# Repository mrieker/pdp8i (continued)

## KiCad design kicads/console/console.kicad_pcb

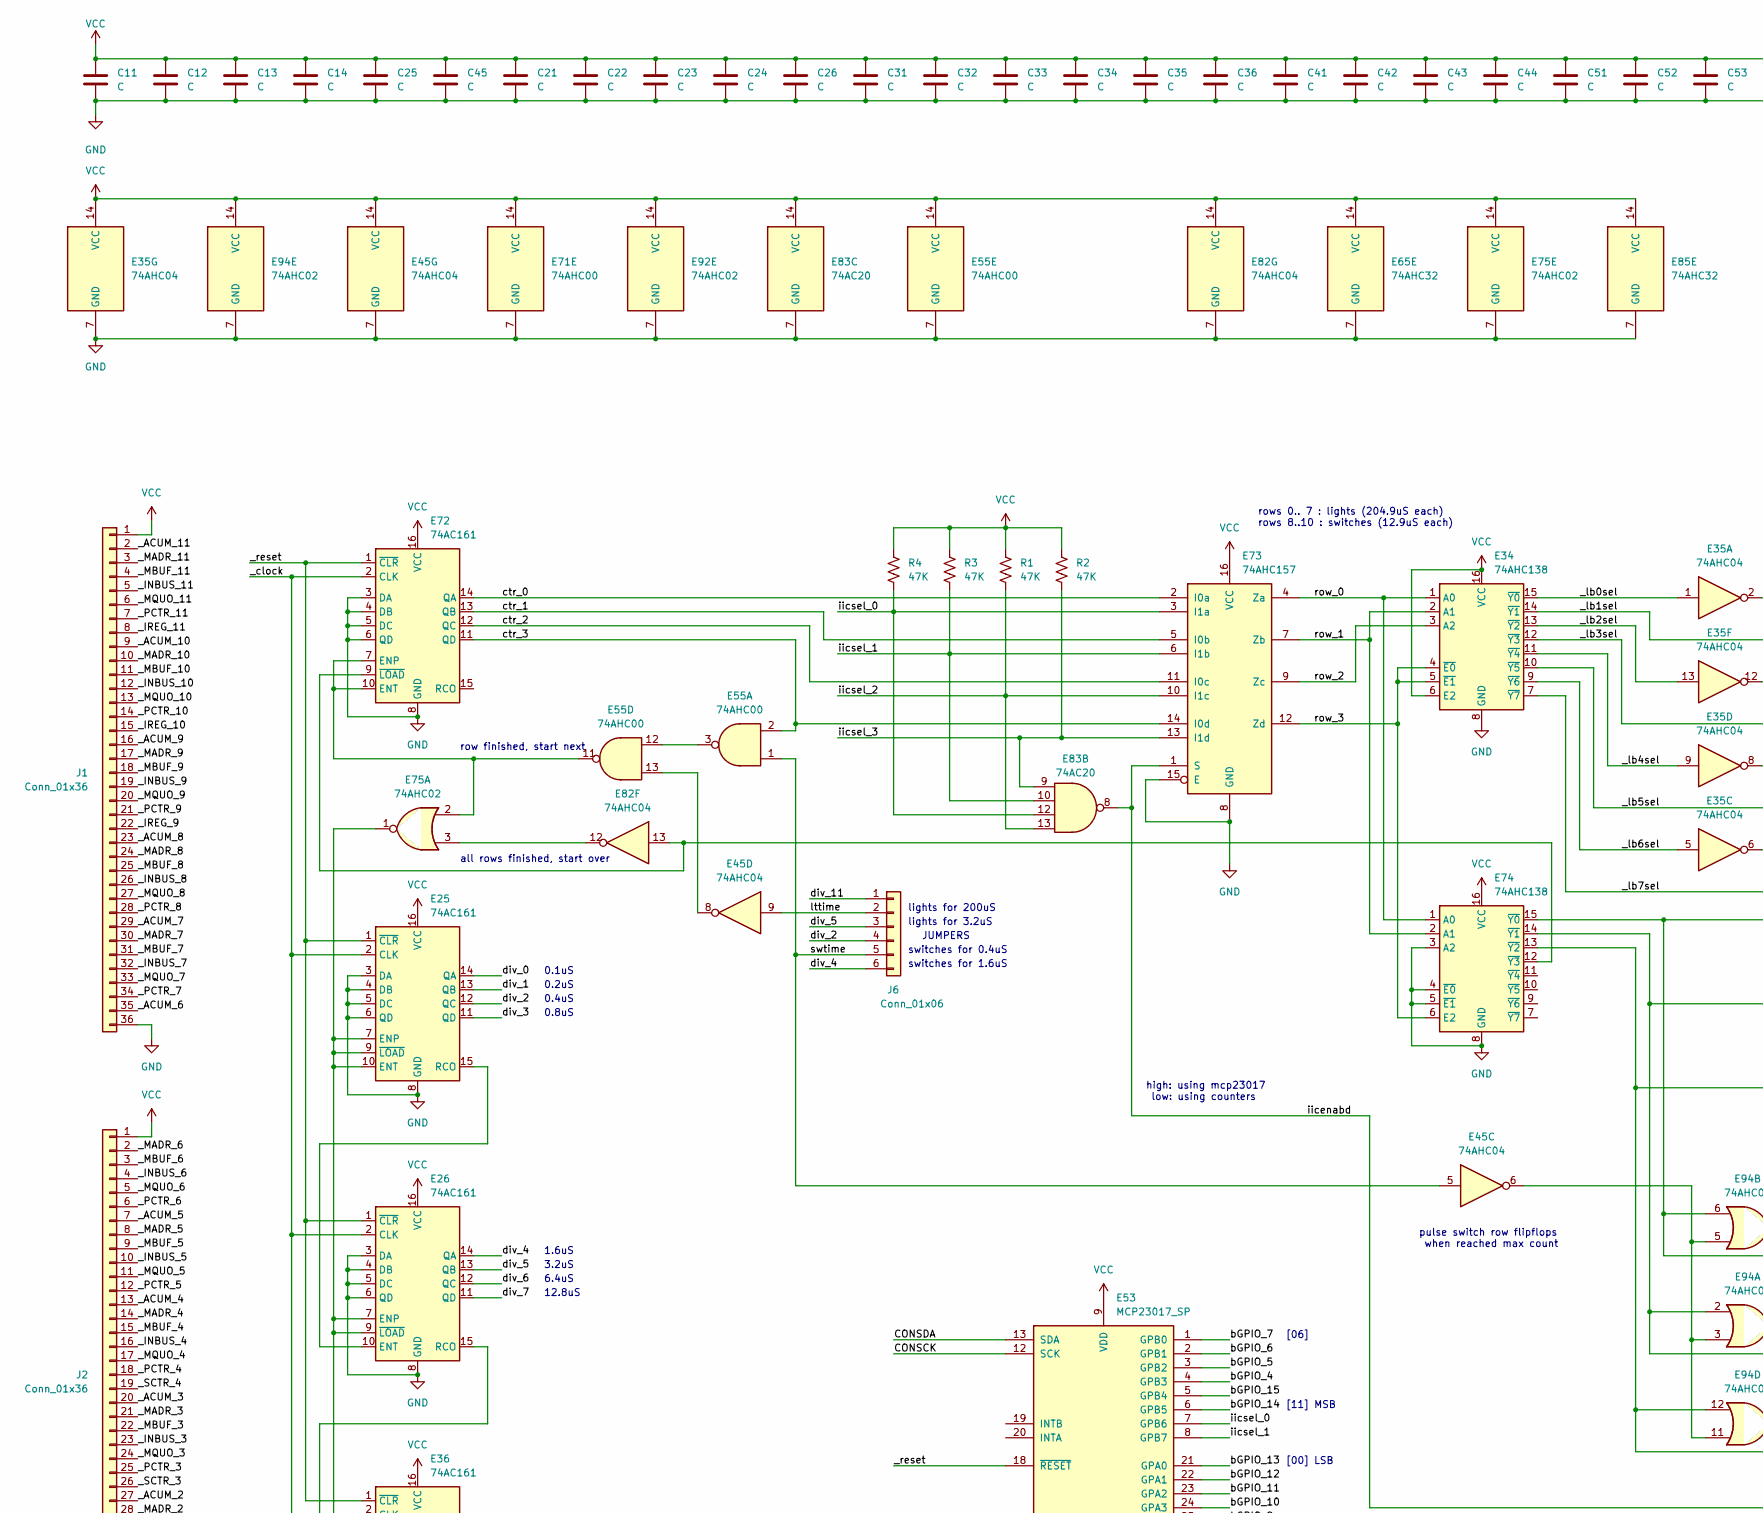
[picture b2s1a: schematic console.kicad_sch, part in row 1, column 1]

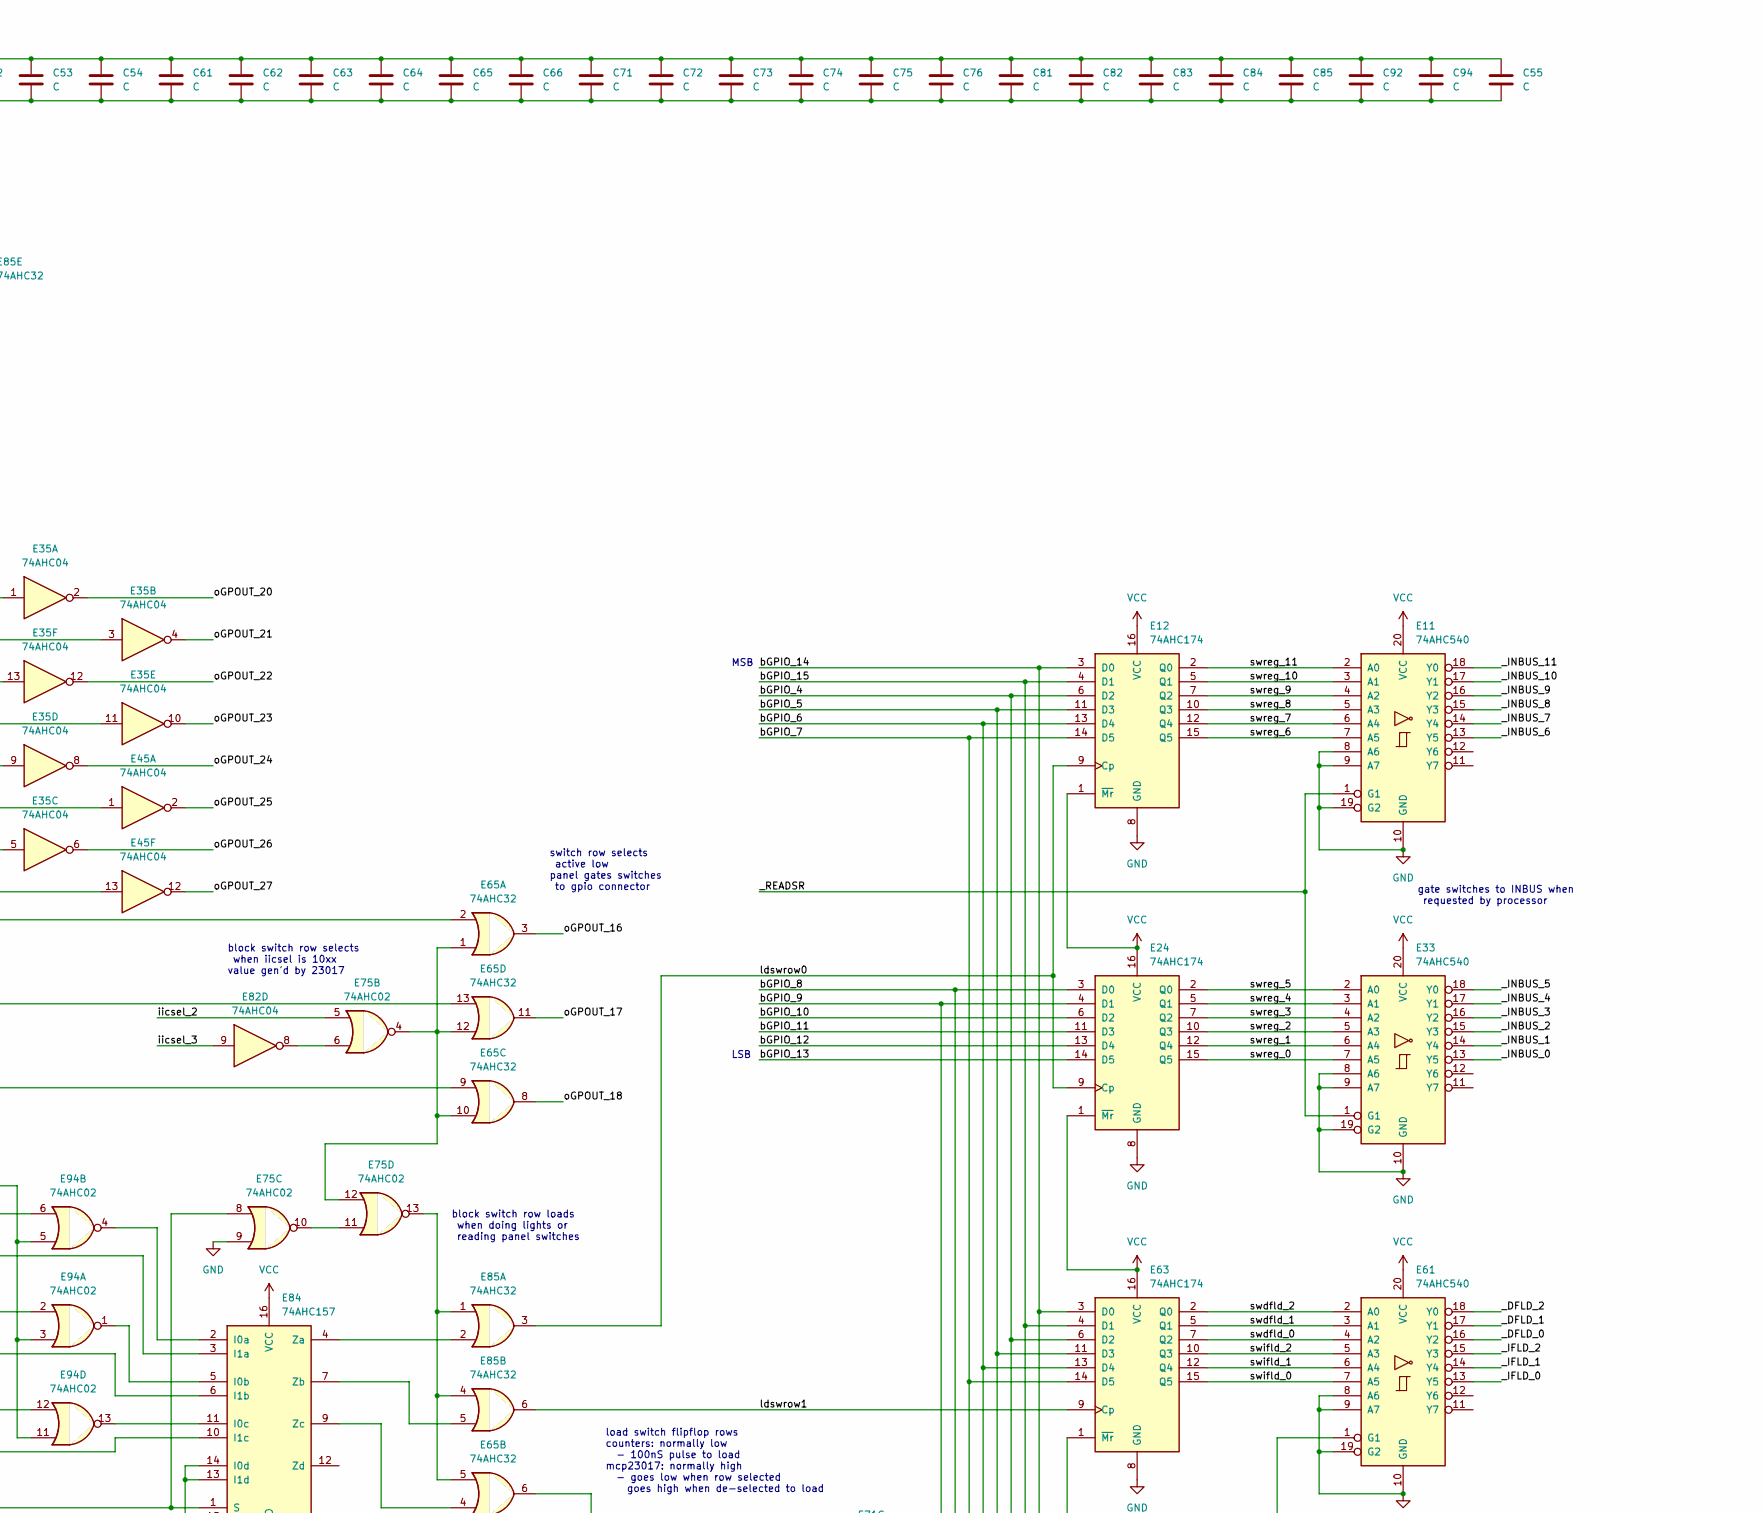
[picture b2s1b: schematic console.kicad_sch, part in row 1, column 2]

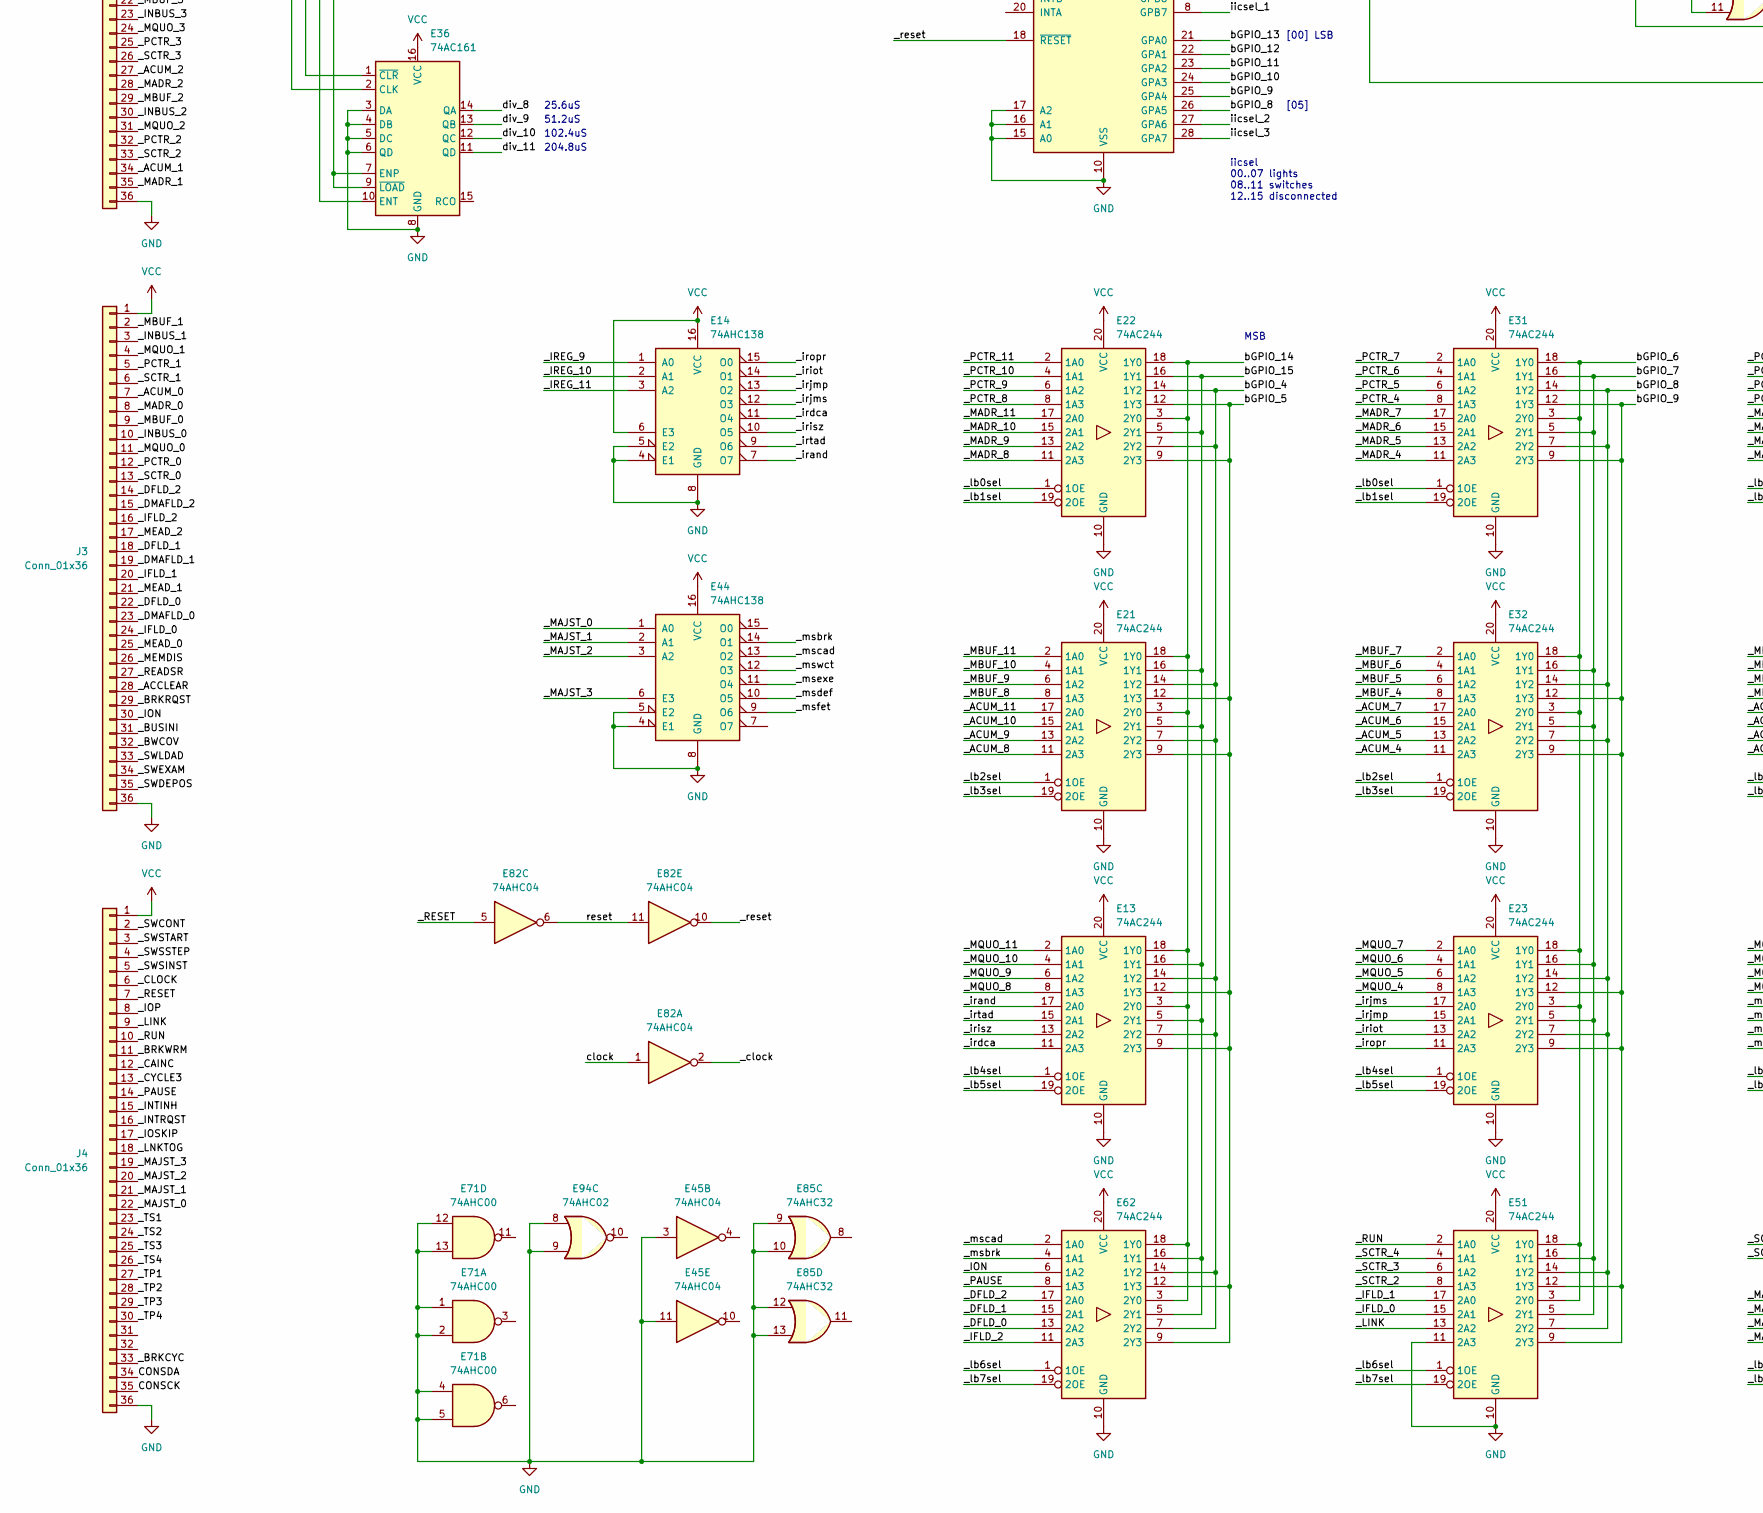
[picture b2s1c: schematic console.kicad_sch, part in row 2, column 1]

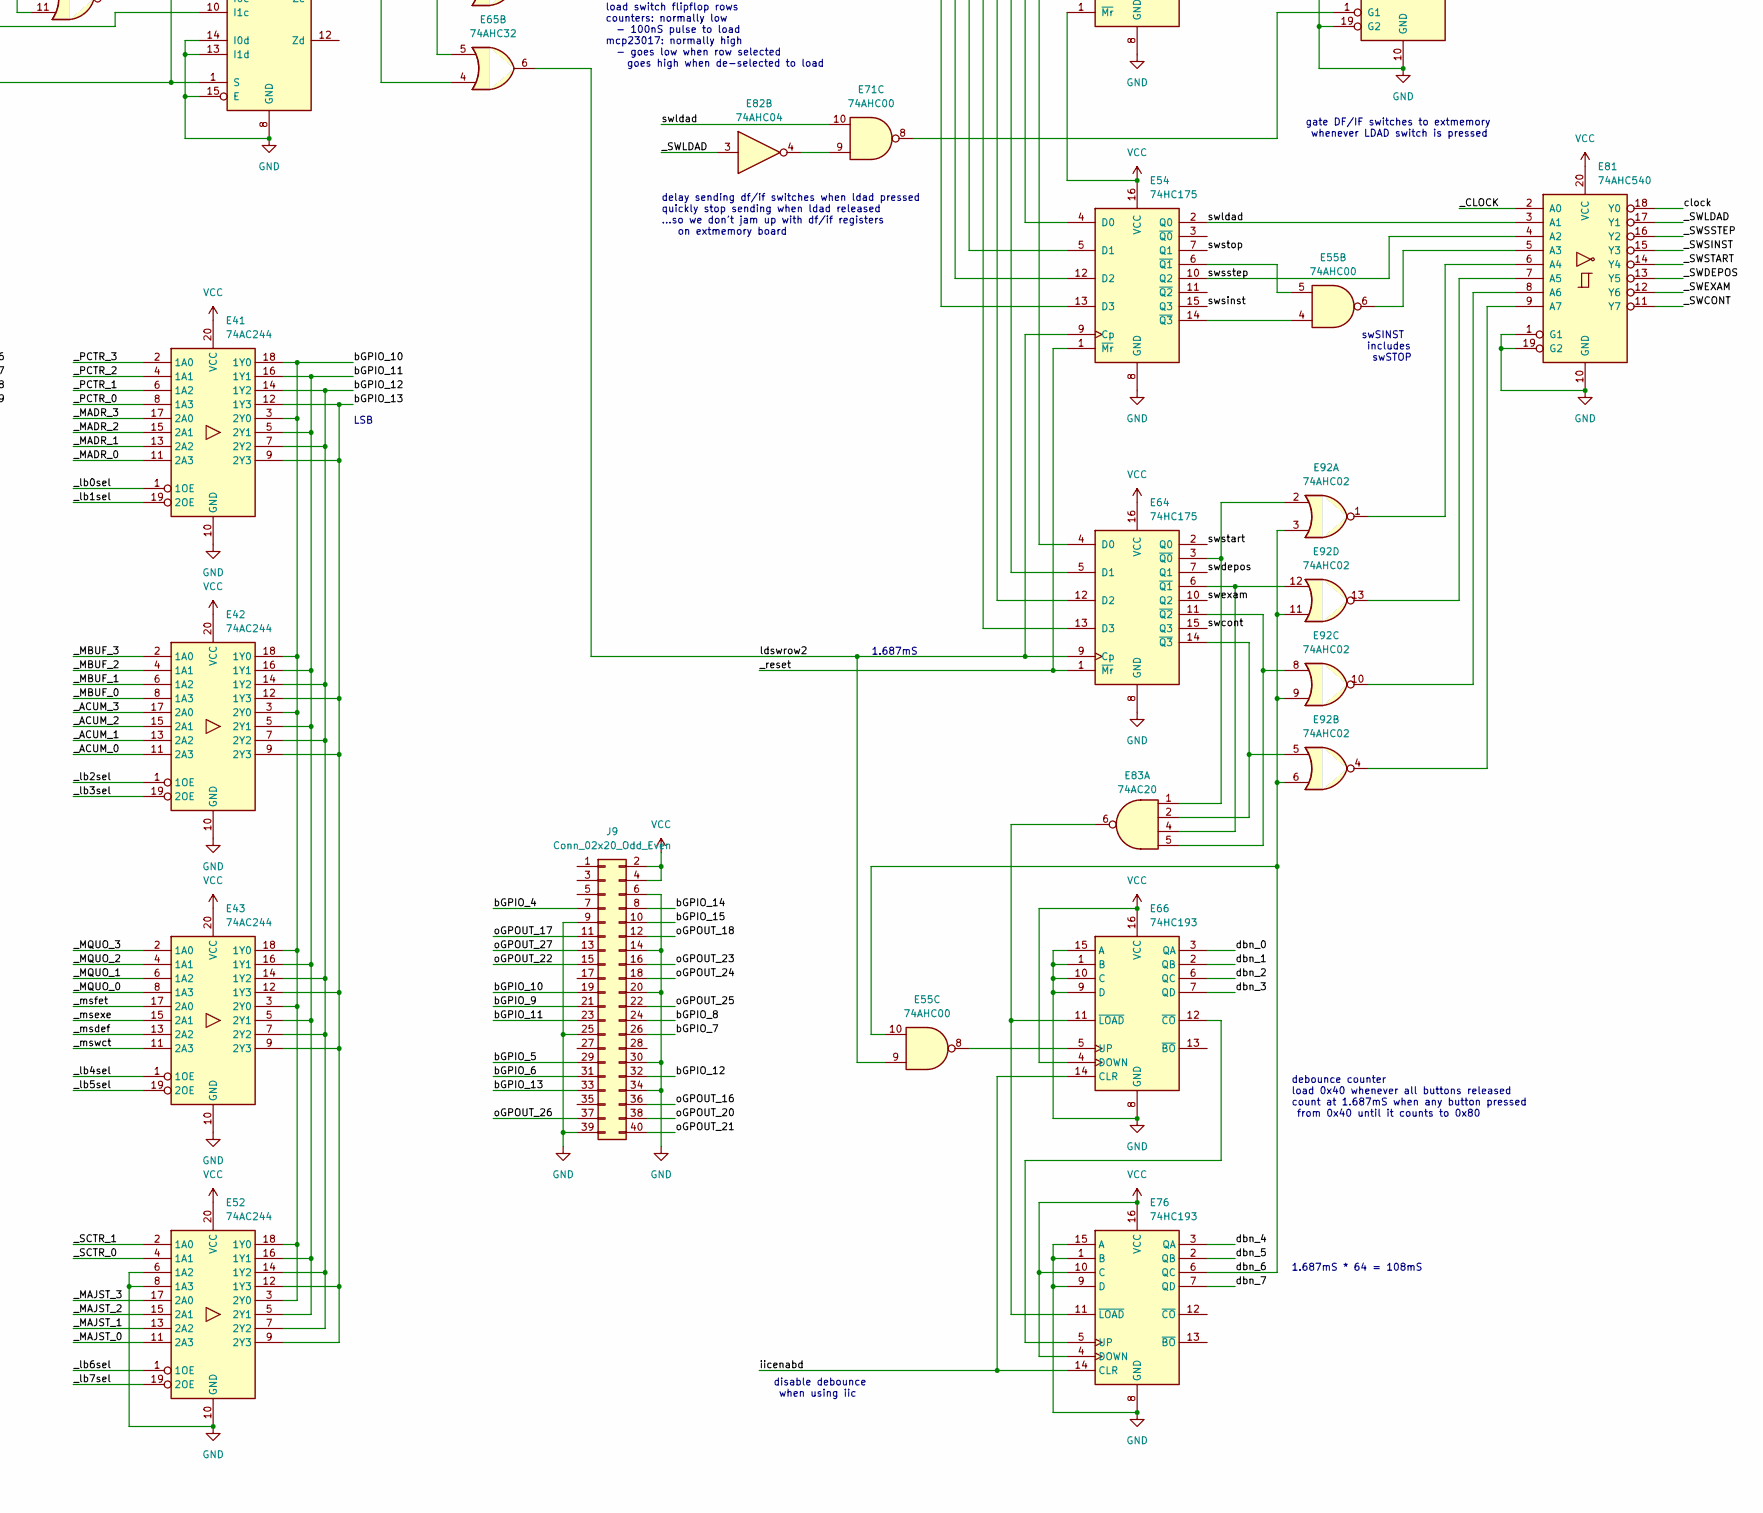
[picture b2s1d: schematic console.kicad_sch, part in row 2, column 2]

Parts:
C11, C12, C13, C14, C21, C22, C23, C24, C25, C26, C31, C32, C33, C34, C35, C36, C41, C42, C43, C44, C45, C51, C52, C53, C54, C55, C61, C62, C63, C64, C65, C66, C71, C72, C73, C74, C75, C76, C81, C82, C83, C84, C85, C92, C94: C; R_Axial_DIN0207_L6.3mm_D2.5mm_P7.62mm_Horizontal
E11, E33, E61, E81: 74AHC540; DIP-20_W7.62mm
E12, E24, E63: 74AHC174; DIP-16_W7.62mm
E13, E21, E22, E23, E31, E32, E41, E42, E43, E51, E52, E62: 74AC244; DIP-20_W7.62mm
E14, E34, E44, E74: 74AHC138; DIP-16_W7.62mm
E25, E26, E36, E72: 74AC161; DIP-16_W7.62mm
E35, E45, E82: 74AHC04; DIP-14_W7.62mm
E53: MCP23017_SP; DIP-28_W7.62mm
E54, E64: 74HC175; DIP-16_W7.62mm
E55, E71: 74AHC00; DIP-14_W7.62mm
E65, E85: 74AHC32; DIP-14_W7.62mm
E66, E76: 74HC193; DIP-16_W7.62mm
E73, E84: 74AHC157; DIP-16_W7.62mm
E75, E92: 74AHC02
E83: 74AC20; DIP-14_W7.62mm
E94: 74AHC02; DIP-14_W7.62mm
J1, J2, J3, J4: Conn_01x36; PinHeader_1x36_P2.54mm_Vertical
J6: Conn_01x06; PinHeader_1x06_P2.54mm_Vertical
J9: Conn_02x20_Odd_Even; PinHeader_2x20_P2.54mm_Vertical
R1, R2, R3, R4: 47K; R_Axial_DIN0207_L6.3mm_D2.5mm_P7.62mm_Horizontal

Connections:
/CONSCK: E53.12 (SCK), J4.35
/CONSDA: E53.13 (SDA), J4.34
/_ACCLEAR: J3.28
/_ACUM_0: E42.11 (2A3), J3.7
/_ACUM_1: E42.13 (2A2), J2.34
/_ACUM_2: E42.15 (2A1), J2.27
/_ACUM_3: E42.17 (2A0), J2.20
/_ACUM_4: E32.11 (2A3), J2.13
/_ACUM_5: E32.13 (2A2), J2.7
/_ACUM_6: E32.15 (2A1), J1.35
/_ACUM_7: E32.17 (2A0), J1.29
/_ACUM_8: E21.11 (2A3), J1.23
/_ACUM_9: E21.13 (2A2), J1.16
/_ACUM_10: E21.15 (2A1), J1.9
/_ACUM_11: E21.17 (2A0), J1.2
/_BRKCYC: J4.33
/_BRKRQST: J3.29
/_BRKWRM: J4.11
/_BUSINI: J3.31
/_BWCOV: J3.32
/_CAINC: J4.12
/_CLOCK: E81.2 (A0), J4.6
/_CYCLE3: J4.13
/_DFLD_0: E61.16 (Y2), E62.13 (2A2), J3.22
/_DFLD_1: E61.17 (Y1), E62.15 (2A1), J3.18
/_DFLD_2: E61.18 (Y0), E62.17 (2A0), J3.14
/_DMAFLD_0: J3.23
/_DMAFLD_1: J3.19
/_DMAFLD_2: J3.15
/_IFLD_0: E51.15 (2A1), E61.13 (Y5), J3.24
/_IFLD_1: E51.17 (2A0), E61.14 (Y4), J3.20
/_IFLD_2: E61.15 (Y3), E62.11 (2A3), J3.16
/_INBUS_0: E33.13 (Y5), J3.10
/_INBUS_1: E33.14 (Y4), J3.3
/_INBUS_2: E33.15 (Y3), J2.30
/_INBUS_3: E33.16 (Y2), J2.23
/_INBUS_4: E33.17 (Y1), J2.16
/_INBUS_5: E33.18 (Y0), J2.10
/_INBUS_6: E11.13 (Y5), J2.4
/_INBUS_7: E11.14 (Y4), J1.32
/_INBUS_8: E11.15 (Y3), J1.26
/_INBUS_9: E11.16 (Y2), J1.19
/_INBUS_10: E11.17 (Y1), J1.12
/_INBUS_11: E11.18 (Y0), J1.5
/_INTINH: J4.15
/_INTRQST: J4.16
/_ION: E62.6 (1A2), J3.30
/_IOP: J4.8
/_IOSKIP: J4.17
/_IREG_9: E14.1 (A0), J1.22
/_IREG_10: E14.2 (A1), J1.15
/_IREG_11: E14.3 (A2), J1.8
/_LINK: E51.13 (2A2), J4.9
/_LNKTOG: J4.18
/_MADR_0: E41.11 (2A3), J3.8
/_MADR_1: E41.13 (2A2), J2.35
/_MADR_2: E41.15 (2A1), J2.28
/_MADR_3: E41.17 (2A0), J2.21
/_MADR_4: E31.11 (2A3), J2.14
/_MADR_5: E31.13 (2A2), J2.8
/_MADR_6: E31.15 (2A1), J2.2
/_MADR_7: E31.17 (2A0), J1.30
/_MADR_8: E22.11 (2A3), J1.24
/_MADR_9: E22.13 (2A2), J1.17
/_MADR_10: E22.15 (2A1), J1.10
/_MADR_11: E22.17 (2A0), J1.3
/_MAJST_0: E44.1 (A0), E52.11 (2A3), J4.22
/_MAJST_1: E44.2 (A1), E52.13 (2A2), J4.21
/_MAJST_2: E44.3 (A2), E52.15 (2A1), J4.20
/_MAJST_3: E44.6 (E3), E52.17 (2A0), J4.19
/_MBUF_0: E42.8 (1A3), J3.9
/_MBUF_1: E42.6 (1A2), J3.2
/_MBUF_2: E42.4 (1A1), J2.29
/_MBUF_3: E42.2 (1A0), J2.22
/_MBUF_4: E32.8 (1A3), J2.15
/_MBUF_5: E32.6 (1A2), J2.9
/_MBUF_6: E32.4 (1A1), J2.3
/_MBUF_7: E32.2 (1A0), J1.31
/_MBUF_8: E21.8 (1A3), J1.25
/_MBUF_9: E21.6 (1A2), J1.18
/_MBUF_10: E21.4 (1A1), J1.11
/_MBUF_11: E21.2 (1A0), J1.4
/_MEAD_0: J3.25
/_MEAD_1: J3.21
/_MEAD_2: J3.17
/_MEMDIS: J3.26
/_MQUO_0: E43.8 (1A3), J3.11
/_MQUO_1: E43.6 (1A2), J3.4
/_MQUO_2: E43.4 (1A1), J2.31
/_MQUO_3: E43.2 (1A0), J2.24
/_MQUO_4: E23.8 (1A3), J2.17
/_MQUO_5: E23.6 (1A2), J2.11
/_MQUO_6: E23.4 (1A1), J2.5
/_MQUO_7: E23.2 (1A0), J1.33
/_MQUO_8: E13.8 (1A3), J1.27
/_MQUO_9: E13.6 (1A2), J1.20
/_MQUO_10: E13.4 (1A1), J1.13
/_MQUO_11: E13.2 (1A0), J1.6
/_PAUSE: E62.8 (1A3), J4.14
/_PCTR_0: E41.8 (1A3), J3.12
/_PCTR_1: E41.6 (1A2), J3.5
/_PCTR_2: E41.4 (1A1), J2.32
/_PCTR_3: E41.2 (1A0), J2.25
/_PCTR_4: E31.8 (1A3), J2.18
/_PCTR_5: E31.6 (1A2), J2.12
/_PCTR_6: E31.4 (1A1), J2.6
/_PCTR_7: E31.2 (1A0), J1.34
/_PCTR_8: E22.8 (1A3), J1.28
/_PCTR_9: E22.6 (1A2), J1.21
/_PCTR_10: E22.4 (1A1), J1.14
/_PCTR_11: E22.2 (1A0), J1.7
/_READSR: E11.1 (G1), E33.1 (G1), J3.27
/_RESET: E82.5, J4.7
/_RUN: E51.2 (1A0), J4.10
/_SCTR_0: E52.4 (1A1), J3.13
/_SCTR_1: E52.2 (1A0), J3.6
/_SCTR_2: E51.8 (1A3), J2.33
/_SCTR_3: E51.6 (1A2), J2.26
/_SCTR_4: E51.4 (1A1), J2.19
/_SWCONT: E81.11 (Y7), J4.2
/_SWDEPOS: E81.13 (Y5), J3.35
/_SWEXAM: E81.12 (Y6), J3.34
/_SWLDAD: E81.17 (Y1), E82.3, J3.33
/_SWSINST: E81.15 (Y3), J4.5
/_SWSSTEP: E81.16 (Y2), J4.4
/_SWSTART: E81.14 (Y4), J4.3
/_TP1: J4.27
/_TP2: J4.28
/_TP3: J4.29
/_TP4: J4.30
/_TS1: J4.23
/_TS2: J4.24
/_TS3: J4.25
/_TS4: J4.26
/_clock: E25.2 (CLK), E26.2 (CLK), E36.2 (CLK), E72.2 (CLK), E82.2
/_irand: E13.17 (2A0), E14.7 (O7)
/_irdca: E13.11 (2A3), E14.11 (O4)
/_iriot: E14.14 (O1), E23.13 (2A2)
/_irisz: E13.13 (2A2), E14.10 (O5)
/_irjmp: E14.13 (O2), E23.15 (2A1)
/_irjms: E14.12 (O3), E23.17 (2A0)
/_iropr: E14.15 (O0), E23.11 (2A3)
/_irtad: E13.15 (2A1), E14.9 (O6)
/_lb0sel: E22.1 (1OE), E31.1 (1OE), E34.15 (~Y0), E35.1, E41.1 (1OE)
/_lb1sel: E22.19 (2OE), E31.19 (2OE), E34.14 (~Y1), E35.3, E41.19 (2OE)
/_lb2sel: E21.1 (1OE), E32.1 (1OE), E34.13 (~Y2), E35.13, E42.1 (1OE)
/_lb3sel: E21.19 (2OE), E32.19 (2OE), E34.12 (~Y3), E35.11, E42.19 (2OE)
/_lb4sel: E13.1 (1OE), E23.1 (1OE), E34.11 (~Y4), E35.9, E43.1 (1OE)
/_lb5sel: E13.19 (2OE), E23.19 (2OE), E34.10 (~Y5), E43.19 (2OE), E45.1
/_lb6sel: E34.9 (~Y6), E35.5, E51.1 (1OE), E52.1 (1OE), E62.1 (1OE)
/_lb7sel: E34.7 (~Y7), E45.13, E51.19 (2OE), E52.19 (2OE), E62.19 (2OE)
/_msbrk: E44.14 (O1), E62.4 (1A1)
/_mscad: E44.13 (O2), E62.2 (1A0)
/_msdef: E43.13 (2A2), E44.10 (O5)
/_msexe: E43.15 (2A1), E44.11 (O4)
/_msfet: E43.17 (2A0), E44.9 (O6)
/_mswct: E43.11 (2A3), E44.12 (O3)
/_reset: E25.1 (~CLR), E26.1 (~CLR), E36.1 (~CLR), E53.18 (~RESET), E54.1 (~Mr), E64.1 (~Mr), E72.1 (~CLR), E82.10
/bGPIO_4: E12.6 (D2), E13.7 (2Y2), E13.14 (1Y2), E21.7 (2Y2), E21.14 (1Y2), E22.7 (2Y2), E22.14 (1Y2), E53.4 (GPB3), E62.7 (2Y2), E62.14 (1Y2), E63.6 (D2), E64.5 (D1), J9.7
/bGPIO_5: E12.11 (D3), E13.9 (2Y3), E13.12 (1Y3), E21.9 (2Y3), E21.12 (1Y3), E22.9 (2Y3), E22.12 (1Y3), E53.3 (GPB2), E62.9 (2Y3), E62.12 (1Y3), E63.11 (D3), E64.12 (D2), J9.29
/bGPIO_6: E12.13 (D4), E23.3 (2Y0), E23.18 (1Y0), E31.3 (2Y0), E31.18 (1Y0), E32.3 (2Y0), E32.18 (1Y0), E51.3 (2Y0), E51.18 (1Y0), E53.2 (GPB1), E63.13 (D4), E64.13 (D3), J9.31
/bGPIO_7: E12.14 (D5), E23.5 (2Y1), E23.16 (1Y1), E31.5 (2Y1), E31.16 (1Y1), E32.5 (2Y1), E32.16 (1Y1), E51.5 (2Y1), E51.16 (1Y1), E53.1 (GPB0), E54.5 (D1), E63.14 (D5), J9.26
/bGPIO_8: E23.7 (2Y2), E23.14 (1Y2), E24.3 (D0), E31.7 (2Y2), E31.14 (1Y2), E32.7 (2Y2), E32.14 (1Y2), E51.7 (2Y2), E51.14 (1Y2), E53.26 (GPA5), E54.12 (D2), J9.24
/bGPIO_9: E23.9 (2Y3), E23.12 (1Y3), E24.4 (D1), E31.9 (2Y3), E31.12 (1Y3), E32.9 (2Y3), E32.12 (1Y3), E51.9 (2Y3), E51.12 (1Y3), E53.25 (GPA4), E54.13 (D3), J9.21
/bGPIO_10: E24.6 (D2), E41.3 (2Y0), E41.18 (1Y0), E42.3 (2Y0), E42.18 (1Y0), E43.3 (2Y0), E43.18 (1Y0), E52.3 (2Y0), E52.18 (1Y0), E53.24 (GPA3), J9.19
/bGPIO_11: E24.11 (D3), E41.5 (2Y1), E41.16 (1Y1), E42.5 (2Y1), E42.16 (1Y1), E43.5 (2Y1), E43.16 (1Y1), E52.5 (2Y1), E52.16 (1Y1), E53.23 (GPA2), J9.23
/bGPIO_12: E24.13 (D4), E41.7 (2Y2), E41.14 (1Y2), E42.7 (2Y2), E42.14 (1Y2), E43.7 (2Y2), E43.14 (1Y2), E52.7 (2Y2), E52.14 (1Y2), E53.22 (GPA1), J9.32
/bGPIO_13: E24.14 (D5), E41.9 (2Y3), E41.12 (1Y3), E42.9 (2Y3), E42.12 (1Y3), E43.9 (2Y3), E43.12 (1Y3), E52.9 (2Y3), E52.12 (1Y3), E53.21 (GPA0), J9.33
/bGPIO_14: E12.3 (D0), E13.3 (2Y0), E13.18 (1Y0), E21.3 (2Y0), E21.18 (1Y0), E22.3 (2Y0), E22.18 (1Y0), E53.6 (GPB5), E62.3 (2Y0), E62.18 (1Y0), E63.3 (D0), E64.4 (D0), J9.8
/bGPIO_15: E12.4 (D1), E13.5 (2Y1), E13.16 (1Y1), E21.5 (2Y1), E21.16 (1Y1), E22.5 (2Y1), E22.16 (1Y1), E53.5 (GPB4), E54.4 (D0), E62.5 (2Y1), E62.16 (1Y1), E63.4 (D1), J9.10
/clock: E81.18 (Y0), E82.1
/ctr_0: E72.14 (QA), E73.2 (I0a)
/ctr_1: E72.13 (QB), E73.5 (I0b)
/ctr_2: E72.12 (QC), E73.11 (I0c)
/ctr_3: E55.2, E72.11 (QD), E73.14 (I0d)
/dbn_0: E66.3 (QA)
/dbn_1: E66.2 (QB)
/dbn_2: E66.6 (QC)
/dbn_3: E66.7 (QD)
/dbn_4: E76.3 (QA)
/dbn_5: E76.2 (QB)
/dbn_6: E55.10, E76.6 (QC), E92.3, E92.6, E92.9, E92.11
/dbn_7: E76.7 (QD)
/div_0: E25.14 (QA)
/div_1: E25.13 (QB)
/div_2: E25.12 (QC), J6.4
/div_3: E25.11 (QD)
/div_4: E26.14 (QA), J6.6
/div_5: E26.13 (QB), J6.3
/div_6: E26.12 (QC)
/div_7: E26.11 (QD)
/div_8: E36.14 (QA)
/div_9: E36.13 (QB)
/div_10: E36.12 (QC)
/div_11: E36.11 (QD), J6.1
/iicenabd: E66.14 (CLR), E73.1 (S), E75.8, E76.14 (CLR), E83.8, E84.1 (S)
/iicsel_0: E53.7 (GPB6), E73.3 (I1a), E83.12, R4.2
/iicsel_1: E53.8 (GPB7), E73.6 (I1b), E83.10, R3.2
/iicsel_2: E53.27 (GPA6), E73.10 (I1c), E75.5, E83.13, R1.2
/iicsel_3: E53.28 (GPA7), E73.13 (I1d), E82.9, E83.9, R2.2
/ldswrow0: E12.9 (Cp), E24.9 (Cp), E85.3
/ldswrow1: E63.9 (Cp), E85.6
/ldswrow2: E54.9 (Cp), E55.9, E64.9 (Cp), E65.6
/lttime: E45.9, J6.2
/oGPOUT_16: E65.3, J9.36
/oGPOUT_17: E65.11, J9.11
/oGPOUT_18: E65.8, J9.12
/oGPOUT_20: E35.2, J9.38
/oGPOUT_21: E35.4, J9.40
/oGPOUT_22: E35.12, J9.15
/oGPOUT_23: E35.10, J9.16
/oGPOUT_24: E35.8, J9.18
/oGPOUT_25: E45.2, J9.22
/oGPOUT_26: E35.6, J9.37
/oGPOUT_27: E45.12, J9.13
/reset: E82.6, E82.11
/row_0: E34.1 (A0), E73.4 (Za), E74.1 (A0)
/row_1: E34.2 (A1), E73.7 (Zb), E74.2 (A1)
/row_2: E34.3 (A2), E73.9 (Zc)
/row_3: E34.4 (~E0), E34.5 (~E1), E73.12 (Zd), E74.6 (E2)
/swcont: E64.15 (Q3)
/swdepos: E64.7 (Q1)
/swdfld_0: E61.4 (A2), E63.7 (Q2)
/swdfld_1: E61.3 (A1), E63.5 (Q1)
/swdfld_2: E61.2 (A0), E63.2 (Q0)
/swexam: E64.10 (Q2)
/swifld_0: E61.7 (A5), E63.15 (Q5)
/swifld_1: E61.6 (A4), E63.12 (Q4)
/swifld_2: E61.5 (A3), E63.10 (Q3)
/swldad: E54.2 (Q0), E71.10, E81.3 (A1)
/swreg_0: E24.15 (Q5), E33.7 (A5)
/swreg_1: E24.12 (Q4), E33.6 (A4)
/swreg_2: E24.10 (Q3), E33.5 (A3)
/swreg_3: E24.7 (Q2), E33.4 (A2)
/swreg_4: E24.5 (Q1), E33.3 (A1)
/swreg_5: E24.2 (Q0), E33.2 (A0)
/swreg_6: E11.7 (A5), E12.15 (Q5)
/swreg_7: E11.6 (A4), E12.12 (Q4)
/swreg_8: E11.5 (A3), E12.10 (Q3)
/swreg_9: E11.4 (A2), E12.7 (Q2)
/swreg_10: E11.3 (A1), E12.5 (Q1)
/swreg_11: E11.2 (A0), E12.2 (Q0)
/swsinst: E54.15 (Q3)
/swsstep: E54.10 (Q2), E81.4 (A2)
/swstart: E64.2 (Q0)
/swstop: E54.7 (Q1)
/swtime: E45.5, E55.1, J6.5
GND: C11.2, C12.2, C13.2, C14.2, C21.2, C22.2, C23.2, C24.2, C25.2, C26.2, C31.2, C32.2, C33.2, C34.2, C35.2, C36.2, C41.2, C42.2, C43.2, C44.2, C45.2, C51.2, C52.2, C53.2, C54.2, C55.2, C61.2, C62.2, C63.2, C64.2, C65.2, C66.2, C71.2, C72.2, C73.2, C74.2, C75.2, C76.2, C81.2, C82.2, C83.2, C84.2, C85.2, C92.2, C94.2, E11.8 (A6), E11.9 (A7), E11.10 (GND), E11.19 (G2), E12.8 (GND), E13.10 (GND), E14.4 (E1), E14.5 (E2), E14.8 (GND), E21.10 (GND), E22.10 (GND), E23.10 (GND), E24.8 (GND), E25.3 (DA), E25.4 (DB), E25.5 (DC), E25.6 (QD), E25.8 (GND), E26.3 (DA), E26.4 (DB), E26.5 (DC), E26.6 (QD), E26.8 (GND), E31.10 (GND), E32.10 (GND), E33.8 (A6), E33.9 (A7), E33.10 (GND), E33.19 (G2), E34.8 (GND), E35.7 (GND), E36.3 (DA), E36.4 (DB), E36.5 (DC), E36.6 (QD), E36.8 (GND), E41.10 (GND), E42.10 (GND), E43.10 (GND), E44.4 (E1), E44.5 (E2), E44.8 (GND), E45.3, E45.7 (GND), E45.11, E51.10 (GND), E51.11 (2A3), E52.6 (1A2), E52.8 (1A3), E52.10 (GND), E53.10 (VSS), E53.15 (A0), E53.16 (A1), E53.17 (A2), E54.8 (GND), E55.7 (GND), E61.8 (A6), E61.9 (A7), E61.10 (GND), E61.19 (G2), E62.10 (GND), E63.8 (GND), E64.8 (GND), E65.7 (GND), E66.1 (B), E66.8 (GND), E66.9 (D), E66.10 (C), E66.15 (A), E71.1, E71.2, E71.4, E71.5, E71.7 (GND), E71.12, E71.13, E72.3 (DA), E72.4 (DB), E72.5 (DC), E72.6 (QD), E72.8 (GND), E73.8 (GND), E73.15 (E), E74.3 (A2), E74.4 (~E0), E74.5 (~E1), E74.8 (GND), E75.7 (GND), E75.9, E76.1 (B), E76.8 (GND), E76.9 (D), E76.15 (A), E81.1 (G1), E81.10 (GND), E81.19 (G2), E82.7 (GND), E83.7 (GND), E84.8 (GND), E84.13 (I1d), E84.14 (I0d), E84.15 (E), E85.7 (GND), E85.9, E85.10, E85.12, E85.13, E92.7 (GND), E94.7 (GND), E94.8, E94.9, J1.36, J2.36, J3.36, J4.36, J9.6, J9.9, J9.14, J9.20, J9.25, J9.30, J9.34, J9.39
unnamed: E55.11, E72.7 (ENP), E72.10 (ENT), E75.2
unnamed: E72.9 (~LOAD), E74.12 (~Y3), E82.13
unnamed: E25.7 (ENP), E25.9 (~LOAD), E25.10 (ENT), E26.7 (ENP), E26.9 (~LOAD), E36.7 (ENP), E36.9 (~LOAD), E75.1
unnamed: E25.15 (RCO), E26.10 (ENT)
unnamed: E26.15 (RCO), E36.10 (ENT)
unnamed: E45.6, E94.3, E94.5, E94.11
unnamed: E45.8, E55.13
unnamed: E54.6 (~Q1), E55.5
unnamed: E54.14 (~Q3), E55.4
unnamed: E64.3 (~Q0), E83.1, E92.2
unnamed: E64.6 (~Q1), E83.4, E92.12
unnamed: E64.11 (~Q2), E83.5, E92.8
unnamed: E64.14 (~Q3), E83.2, E92.5
unnamed: E55.3, E55.12
unnamed: E61.1 (G1), E71.8
unnamed: E55.8, E66.5 (UP)
unnamed: E66.12 (~CO), E76.5 (UP)
unnamed: E66.11 (~LOAD), E76.11 (~LOAD), E83.6
unnamed: E71.9, E82.4
unnamed: E75.6, E82.8
unnamed: E75.3, E82.12
unnamed: E65.1, E65.10, E65.12, E75.4, E75.12
unnamed: E65.5, E75.13, E85.1, E85.4
unnamed: E84.2 (I0a), E94.4
unnamed: E84.5 (I0b), E94.1
unnamed: E84.11 (I0c), E94.13
unnamed: E65.2, E74.15 (~Y0), E84.3 (I1a), E94.6
unnamed: E65.13, E74.14 (~Y1), E84.6 (I1b), E94.2
unnamed: E65.9, E74.13 (~Y2), E84.10 (I1c), E94.12
unnamed: E84.4 (Za), E85.2
unnamed: E84.7 (Zb), E85.5
unnamed: E65.4, E84.9 (Zc)
unnamed: E75.10, E75.11
unnamed: E55.6, E81.5 (A3)
unnamed: E81.6 (A4), E92.1
unnamed: E81.7 (A5), E92.13
unnamed: E81.8 (A6), E92.10
unnamed: E81.9 (A7), E92.4
VCC: C11.1, C12.1, C13.1, C14.1, C21.1, C22.1, C23.1, C24.1, C25.1, C26.1, C31.1, C32.1, C33.1, C34.1, C35.1, C36.1, C41.1, C42.1, C43.1, C44.1, C45.1, C51.1, C52.1, C53.1, C54.1, C55.1, C61.1, C62.1, C63.1, C64.1, C65.1, C66.1, C71.1, C72.1, C73.1, C74.1, C75.1, C76.1, C81.1, C82.1, C83.1, C84.1, C85.1, C92.1, C94.1, E11.20 (VCC), E12.1 (~Mr), E12.16 (VCC), E13.20 (VCC), E14.6 (E3), E14.16 (VCC), E21.20 (VCC), E22.20 (VCC), E23.20 (VCC), E24.1 (~Mr), E24.16 (VCC), E25.16 (VCC), E26.16 (VCC), E31.20 (VCC), E32.20 (VCC), E33.20 (VCC), E34.6 (E2), E34.16 (VCC), E35.14 (VCC), E36.16 (VCC), E41.20 (VCC), E42.20 (VCC), E43.20 (VCC), E44.16 (VCC), E45.14 (VCC), E51.20 (VCC), E52.20 (VCC), E53.9 (VDD), E54.16 (VCC), E55.14 (VCC), E61.20 (VCC), E62.20 (VCC), E63.1 (~Mr), E63.16 (VCC), E64.16 (VCC), E65.14 (VCC), E66.4 (DOWN), E66.16 (VCC), E71.14 (VCC), E72.16 (VCC), E73.16 (VCC), E74.16 (VCC), E75.14 (VCC), E76.4 (DOWN), E76.10 (C), E76.16 (VCC), E81.20 (VCC), E82.14 (VCC), E83.14 (VCC), E84.16 (VCC), E85.14 (VCC), E92.14 (VCC), E94.14 (VCC), J1.1, J2.1, J3.1, J4.1, J9.2, J9.4, R1.1, R2.1, R3.1, R4.1

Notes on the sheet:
gate switches to INBUS when requested by processor
row finished, start next
pulse switch row flipflops when reached max count
0.8uS
0.4uS
MSB
[05]
gate DF/IF switches to extmemory whenever LDAD switch is pressed
disable debounce when using iic
block switch row loads when doing lights or reading panel switches
12.8uS
[00] LSB
1.687mS * 64 = 108mS
204.8uS
block switch row selects when iicsel is 10xx value gen'd by 23017
25.6uS
[06]
0.2uS
lights for 3.2uS
rows 0.. 7 : lights (204.9uS each) rows 8..10 : switches (12.9uS each)
1.687mS
switch row selects active low panel gates switches to gpio connector
LSB
51.2uS
lights for 200uS
all rows finished, start over
switches for 0.4uS
6.4uS
debounce counter load 0x40 whenever all buttons released count at 1.687mS when any button pressed from 0x40 until it counts to 0x80
3.2uS
high: using mcp23017 low: using counters
102.4uS
delay sending df/if switches when ldad pressed quickly stop sending when ldad released ...so we don't jam up with df/if registers on extmemory board
switches for 1.6uS
[11] MSB
1.6uS
0.1uS
swSINST includes swSTOP
JUMPERS
iicsel 00..07 lights 08..11 switches 12..15 disconnected

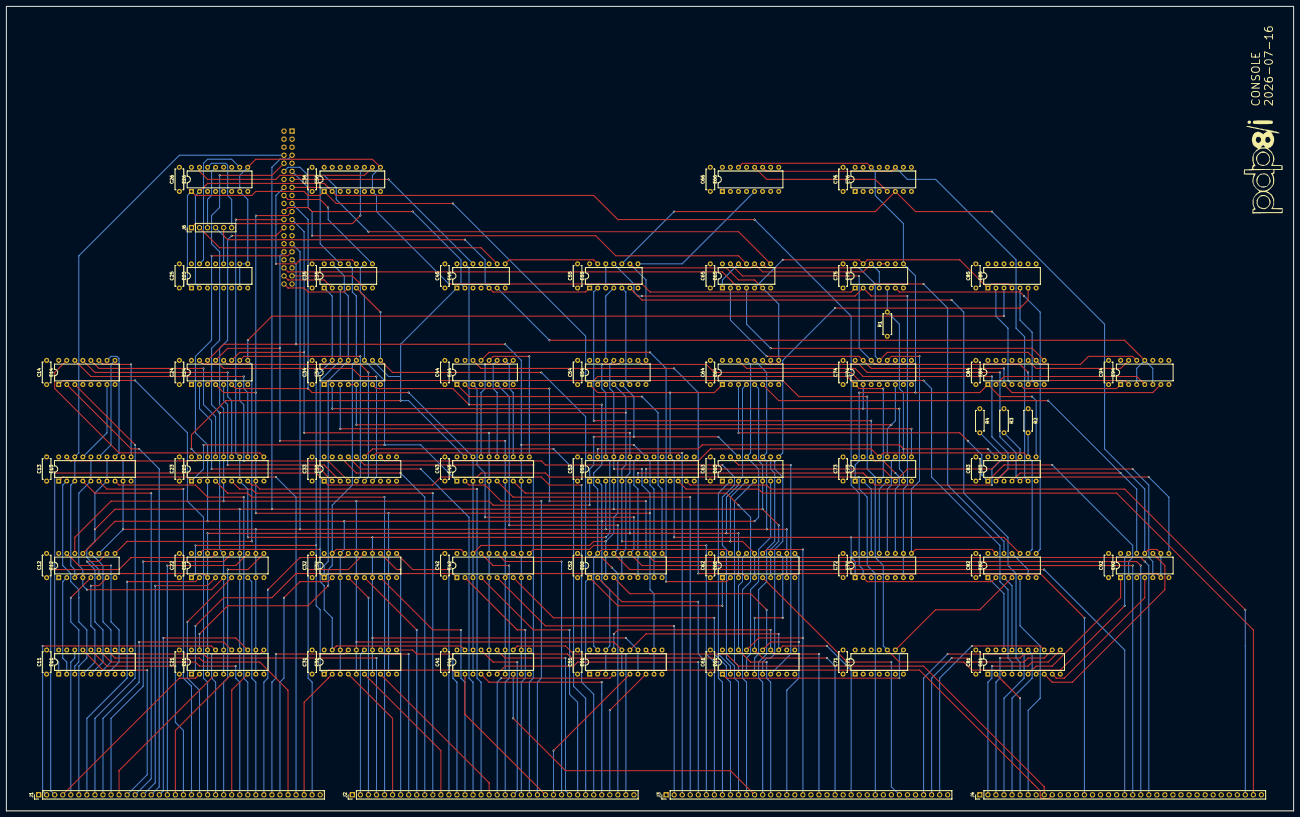
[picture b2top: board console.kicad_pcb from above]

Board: 4 copper layers, 406.4 x 254.0 mm, 100 parts (1 on the bottom side), 238 nets.
